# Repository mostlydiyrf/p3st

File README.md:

# P3ST SSB Transceiver
This repository is for design files, Arduino firmware, and assembly instructions.

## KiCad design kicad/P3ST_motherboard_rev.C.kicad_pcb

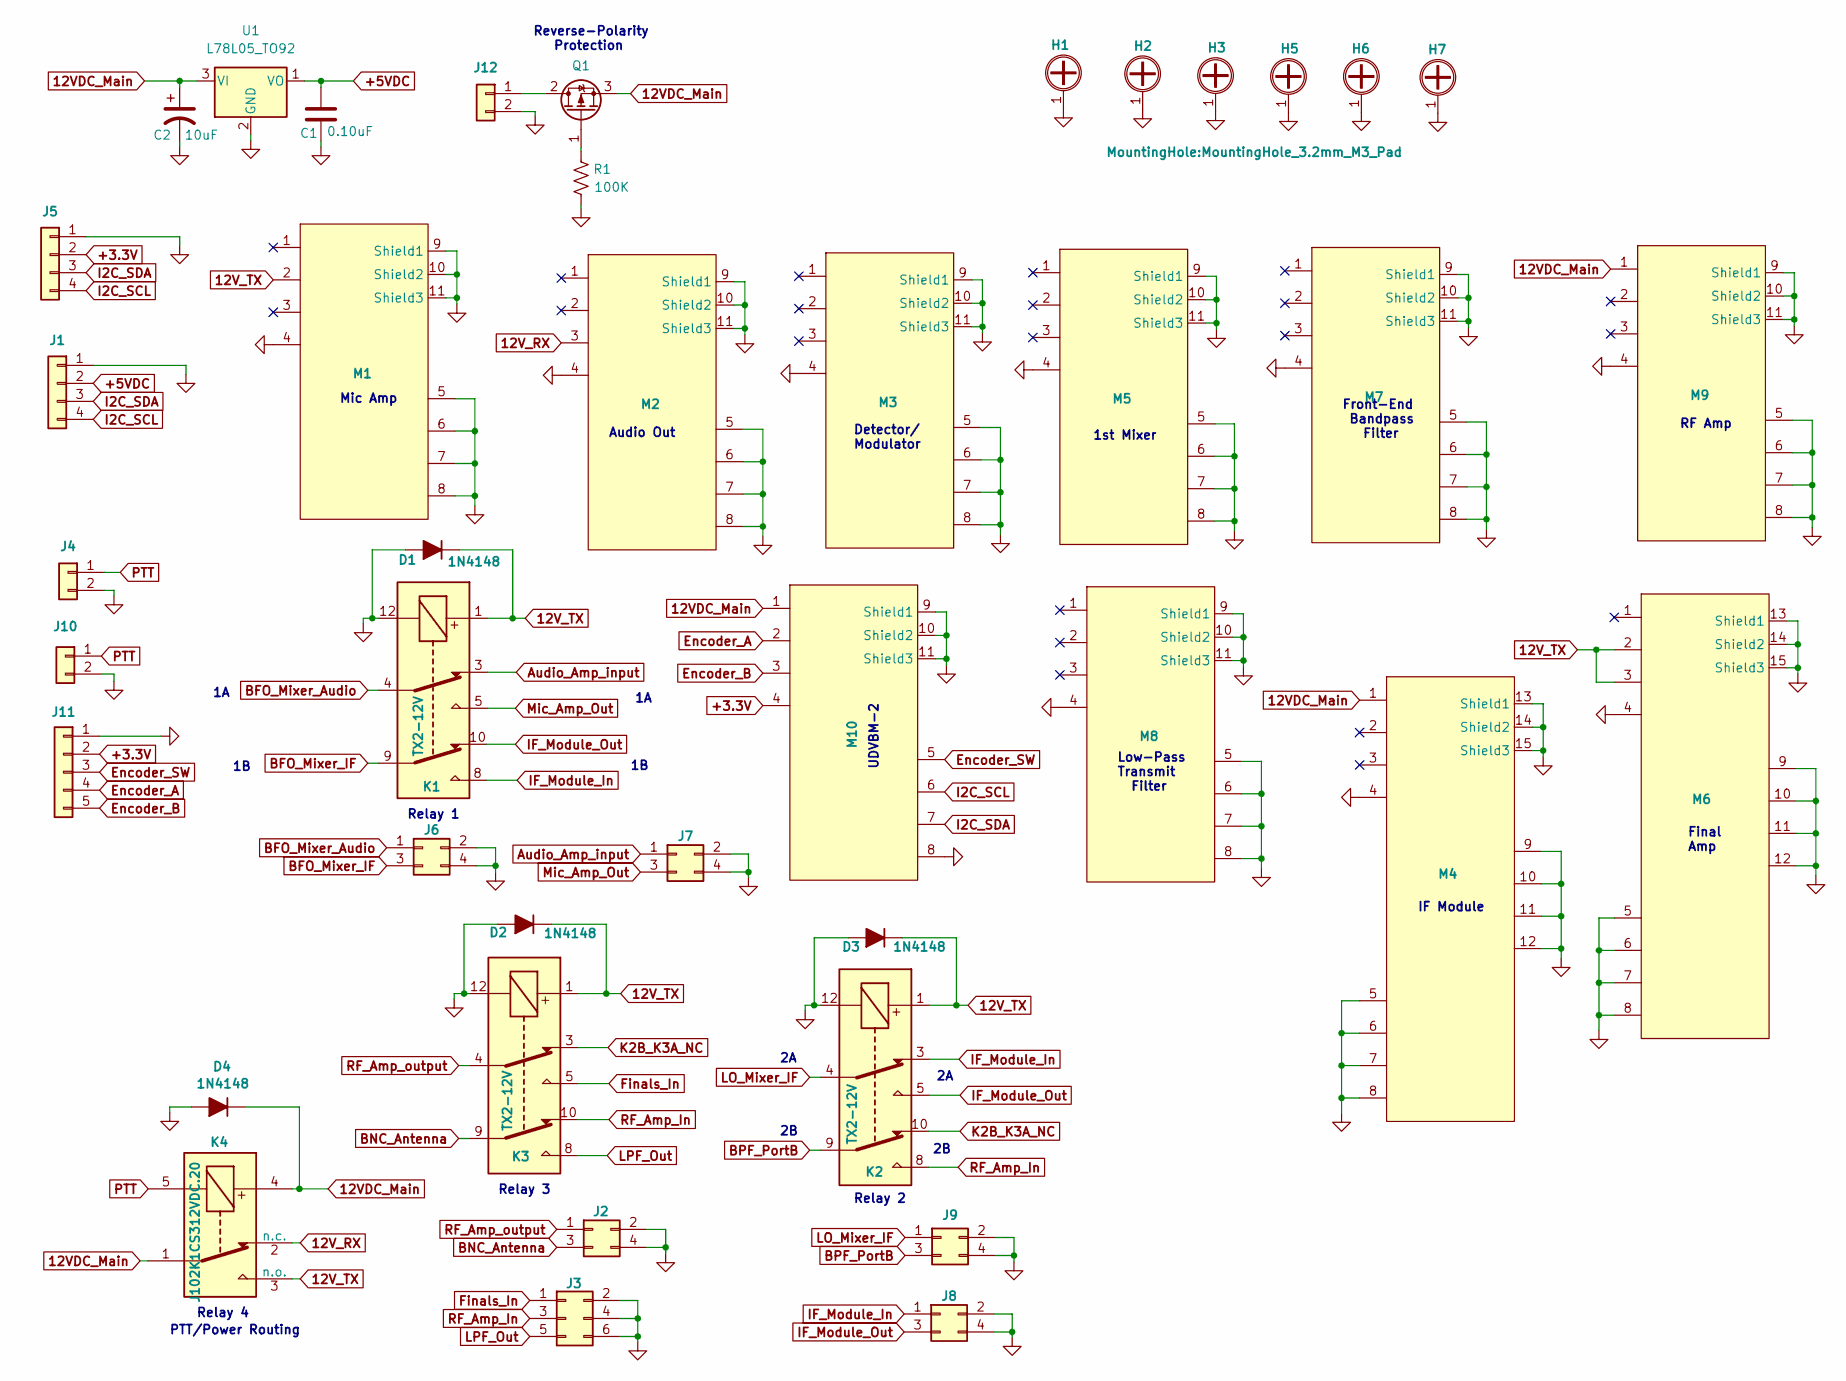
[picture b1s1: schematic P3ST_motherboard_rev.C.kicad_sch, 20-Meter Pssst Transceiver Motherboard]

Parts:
C1: 0.10uF; Ceramic_Disk_Capacitor_P5.00mm
C2: 10uF; CP_Radial_D6.3mm_P2.50mm
D1, D2, D3, D4: 1N4148; D_DO-35_SOD27_P7.62mm_Horizontal
H1, H2, H3, H5, H6, H7: Mounting_Hole_4-40; MountingHole_3.2mm_M3_Pad
J1, J5: Conn_01x04; PinHeader_1x04_P2.54mm_Vertical
J2, J6, J7, J8, J9: Conn_02x02_Odd_Even; RG274_2x2_HS
J3: Conn_02x03_Odd_Even; RG274_2x3_HS
J4, J10, J12: Conn_01x02; PinHeader_1x02_P2.54mm_Vertical
J11: Conn_01x05; PinHeader_1x05_P2.54mm_Vertical
K1, K2, K3: TX2-12V; RELAY_TX2_PAN
K4: J102K1CS312VDC.20; J102K-1C
M1, M2, M7, M8, M9, M10: StandardModule_1; K7TFC_CircuitBlock_Module1
M3, M5: StandardModule_1; K7TFC_CircuitBlock_Half_Module1
M4, M6: StandardModule_2; K7TFC_CircuitBlock_Module2
Q1: MOSFET_P_Channel_GDS; TO-220-3_Vertical
R1: 100K; Resistor_Quarter_Watt_P10.16mm_Horizontal
U1: L78L05_TO92; TO-92_Inline

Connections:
12VDC_Main: C2.1, D4.1 (K), K4.1, K4.4, M4.1, M9.1, M10.1, Q1.3 (S), U1.3 (VI)
12V_RX: K4.2 (n.c.), M2.3
12V_TX: D1.1 (K), D2.1 (K), D3.1 (K), K1.1, K2.1, K3.1, K4.3 (n.o.), M1.2, M6.2, M6.3
+3.3V: J5.2, J11.2, M10.4
+5VDC: C1.1, J1.2, U1.1 (VO)
Audio_Amp_input: J7.1, K1.3
BFO_Mixer_Audio: J6.1, K1.4
BFO_Mixer_IF: J6.3, K1.9
BNC_Antenna: J2.3, K3.9
BPF_PortB: J9.3, K2.9
Encoder_A: J11.4, M10.2
Encoder_B: J11.5, M10.3
Encoder_SW: J11.3, M10.5
Finals_In: J3.1, K3.5
GND: C1.2, C2.2, D1.2 (A), D2.2 (A), D3.2 (A), D4.2 (A), H1.1, H2.1, H3.1, H5.1, H6.1, H7.1, J1.1, J2.2, J2.4, J3.2, J3.4, J3.6, J4.2, J5.1, J6.2, J6.4, J7.2, J7.4, J8.2, J8.4, J9.2, J9.4, J10.2, J11.1, J12.2, K1.12, K2.12, K3.12, M1.4, M1.5, M1.6, M1.7, M1.8, M1.9 (Shield1), M1.10 (Shield2), M1.11 (Shield3), M2.4, M2.5, M2.6, M2.7, M2.8, M2.9 (Shield1), M2.10 (Shield2), M2.11 (Shield3), M3.4, M3.5, M3.6, M3.7, M3.8, M3.9 (Shield1), M3.10 (Shield2), M3.11 (Shield3), M4.4, M4.5, M4.6, M4.7, M4.8, M4.9, M4.10, M4.11, M4.12, M4.13 (Shield1), M4.14 (Shield2), M4.15 (Shield3), M5.4, M5.5, M5.6, M5.7, M5.8, M5.9 (Shield1), M5.10 (Shield2), M5.11 (Shield3), M6.4, M6.5, M6.6, M6.7, M6.8, M6.9, M6.10, M6.11, M6.12, M6.13 (Shield1), M6.14 (Shield2), M6.15 (Shield3), M7.4, M7.5, M7.6, M7.7, M7.8, M7.9 (Shield1), M7.10 (Shield2), M7.11 (Shield3), M8.4, M8.5, M8.6, M8.7, M8.8, M8.9 (Shield1), M8.10 (Shield2), M8.11 (Shield3), M9.4, M9.5, M9.6, M9.7, M9.8, M9.9 (Shield1), M9.10 (Shield2), M9.11 (Shield3), M10.8, M10.9 (Shield1), M10.10 (Shield2), M10.11 (Shield3), R1.2, U1.2 (GND)
I2C_SCL: J1.4, J5.4, M10.6
I2C_SDA: J1.3, J5.3, M10.7
IF_Module_In: J8.1, K1.8, K2.3
IF_Module_Out: J8.3, K1.10, K2.5
K2B_K3A_NC: K2.10, K3.3
LO_Mixer_IF: J9.1, K2.4
LPF_Out: J3.5, K3.8
Mic_Amp_Out: J7.3, K1.5
unnamed: J12.1, Q1.2 (D)
unnamed: Q1.1 (G), R1.1
PTT: J4.1, J10.1, K4.5
RF_Amp_In: J3.3, K2.8, K3.10
RF_Amp_output: J2.1, K3.4

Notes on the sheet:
Relay 3
1st Mixer
Front-End Bandpass Filter
Audio Out
Relay 1
PTT/Power Routing
Final Amp
Mic Amp
Detector/ Modulator
UDVBM-2
RF Amp
Relay 4
IF Module
Reverse-Polarity Protection
Low-Pass Transmit Filter
Relay 2

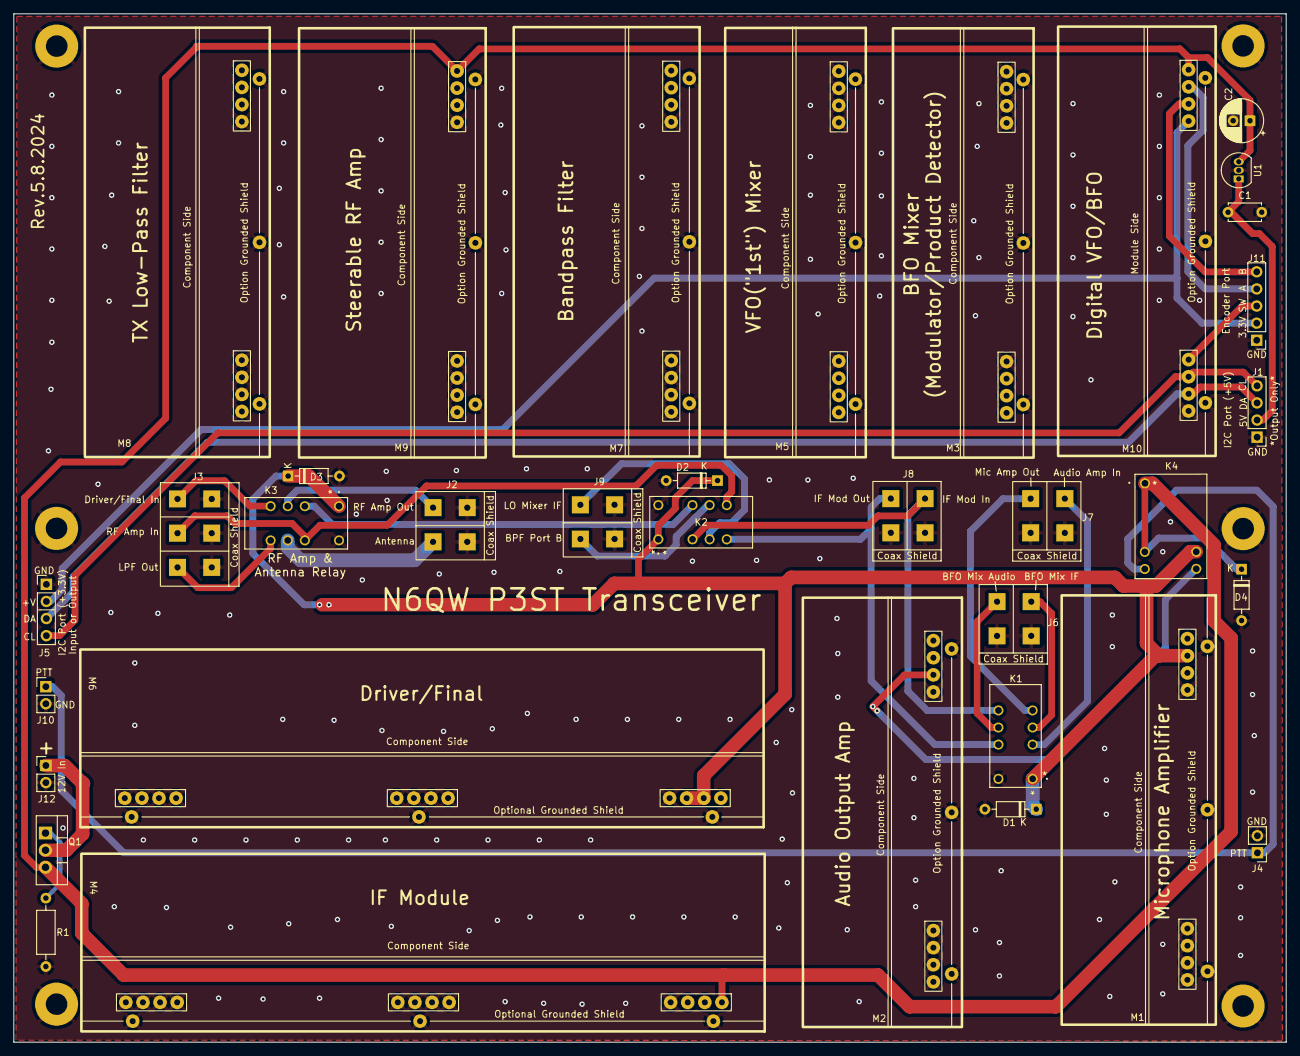
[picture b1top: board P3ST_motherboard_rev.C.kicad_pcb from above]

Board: 2 copper layers, 188.9 x 152.7 mm, 41 parts (0 on the bottom side), 28 nets.

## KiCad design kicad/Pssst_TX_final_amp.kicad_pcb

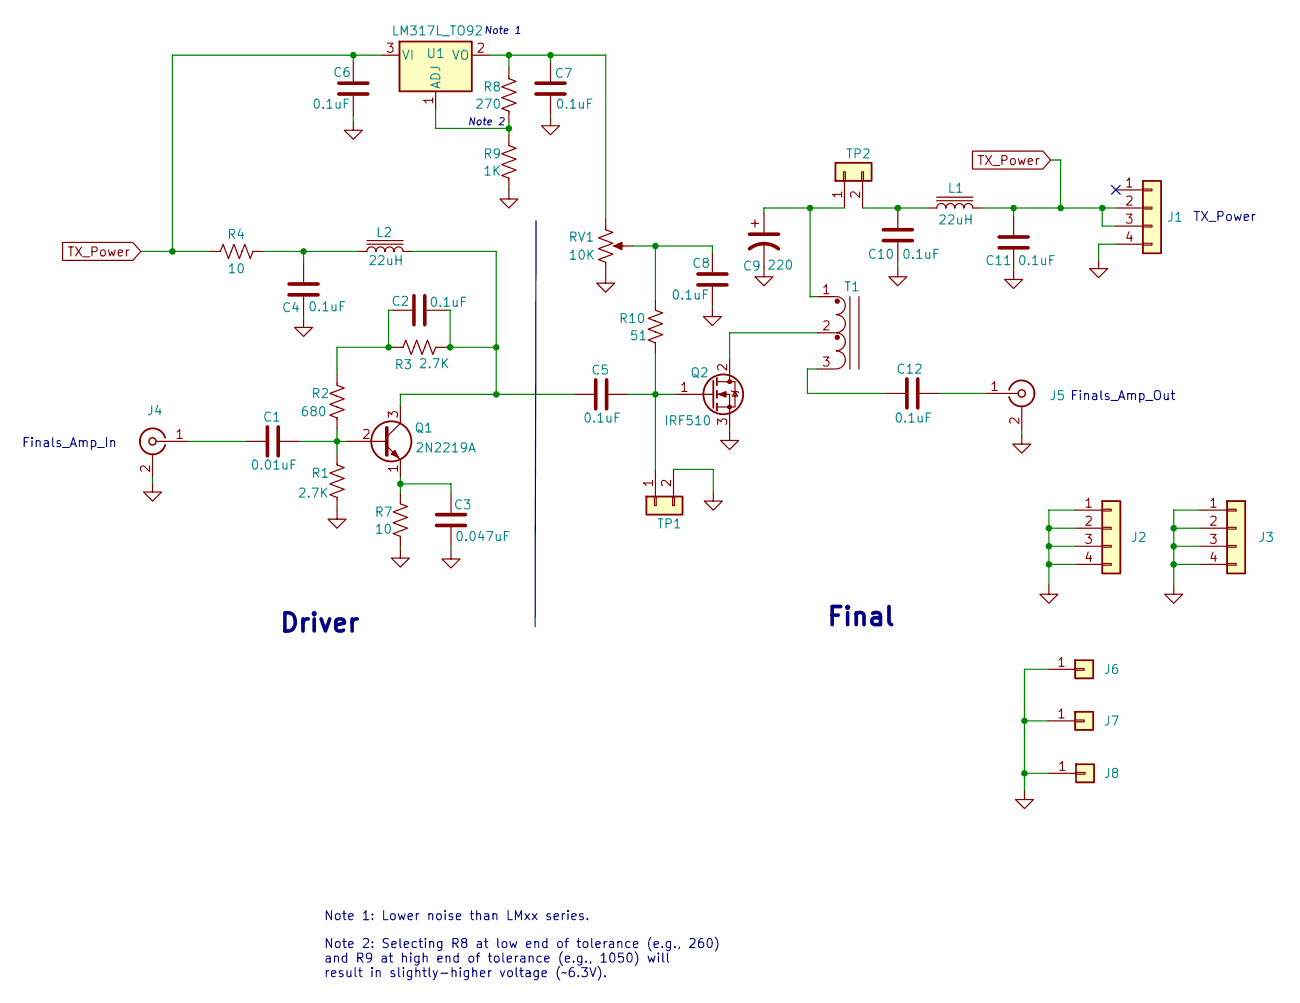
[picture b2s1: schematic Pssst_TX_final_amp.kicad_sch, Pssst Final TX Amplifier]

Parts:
C1: 0.01uF; Ceramic_Disk_Capacitor_P5.00mm
C2, C4, C5, C6, C7, C8, C10, C11, C12: 0.1uF; Ceramic_Disk_Capacitor_P5.00mm
C3: 0.047uF; Ceramic_Disk_Capacitor_P5.00mm
C9: 220; CP_Radial_D5.0mm_P2.50mm
J1, J2, J3: Conn_01x04; PinHeader_1x04_P2.54mm_Vertical
J4, J5: Phono_Jack_RCA; SMA_EdgeMount_0.062_Samtec_wHoles
J6, J7, J8: Conn_01x01; PinHeader_1x01_P2.54mm_Vertical
L1: 22uH; L_Radial_D8.7mm_P5.00mm_Fastron_07HCP
L2: 22uH; L_Axial_L11.0mm_D4.5mm_P15.24mm_Horizontal_Fastron_MECC
Q1: 2N2219A; TO-39-3
Q2: IRF510; TO-220-3_Vertical
R1, R3: 2.7K; Resistor_Quarter_Watt_P10.16mm_Horizontal
R2: 680; Resistor_Quarter_Watt_P10.16mm_Horizontal
R4, R7: 10; Resistor_Quarter_Watt_P10.16mm_Horizontal
R8: 270; Resistor_Quarter_Watt_P10.16mm_Horizontal
R9: 1K; Resistor_Quarter_Watt_P10.16mm_Horizontal
R10: 51; Resistor_Quarter_Watt_P10.16mm_Horizontal
RV1: 10K; POT_Bourns_3362P
T1: Transformer_Bifilar_CT_Toroid; Toroid_Transformer_Bifilar_T50_Vertical_P2.54mm
TP1, TP2: Conn_01x02; PinHeader_1x02_P2.54mm_Vertical
U1: LM317L_TO92; TO-92_Inline

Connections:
GND: C3.1, C4.2, C6.2, C7.2, C8.2, C9.2, C10.2, C11.2, J1.4, J2.1, J2.2, J2.3, J2.4, J3.1, J3.2, J3.3, J3.4, J4.2 (Ext), J5.2 (Ext), J6.1, J7.1, J8.1, Q2.3 (S), R1.2, R7.2, R9.2, RV1.3, TP1.2
unnamed: C1.1, Q1.2 (B), R1.1, R2.2
unnamed: C1.2, J4.1 (In)
unnamed: C2.1, R2.1, R3.1
unnamed: C2.2, C5.2, L2.2, Q1.3 (C), R3.2
unnamed: C3.2, Q1.1 (E), R7.1
unnamed: C4.1, L2.1, R4.2
unnamed: C5.1, Q2.1 (G), R10.2, TP1.1
unnamed: C7.1, R8.1, RV1.1, U1.2 (VO)
unnamed: C8.1, R10.1, RV1.2
unnamed: C9.1, T1.1 (PR1), TP2.1
unnamed: C10.1, L1.1, TP2.2
unnamed: C12.1, T1.3 (PR2)
unnamed: C12.2, J5.1 (In)
unnamed: Q2.2 (D), T1.2 (PM)
unnamed: R8.2, R9.1, U1.1 (ADJ)
TX_Power: C6.1, C11.1, J1.2, J1.3, L1.2, R4.1, U1.3 (VI)

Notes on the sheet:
Driver
Note 2
Note 2: Selecting R8 at low end of tolerance (e.g., 260) and R9 at high end of tolerance (e.g., 1050) will result in slightly-higher voltage (~6.3V).
Finals_Amp_Out
Finals_Amp_In
Final
Note 1: Lower noise than LMxx series.
Note 1
TX_Power

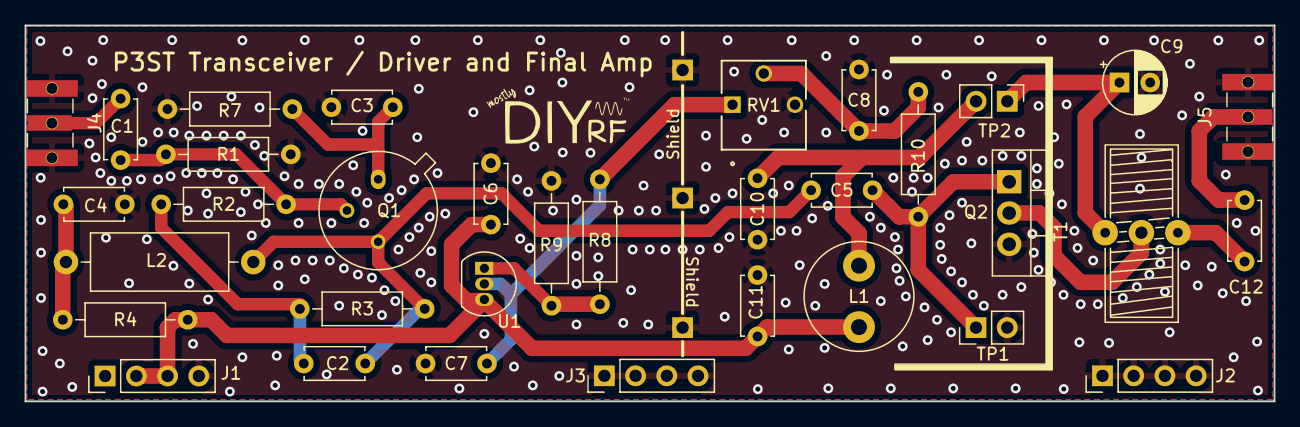
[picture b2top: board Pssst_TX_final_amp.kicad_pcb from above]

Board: 2 copper layers, 101.6 x 30.6 mm, 37 parts (0 on the bottom side), 17 nets.

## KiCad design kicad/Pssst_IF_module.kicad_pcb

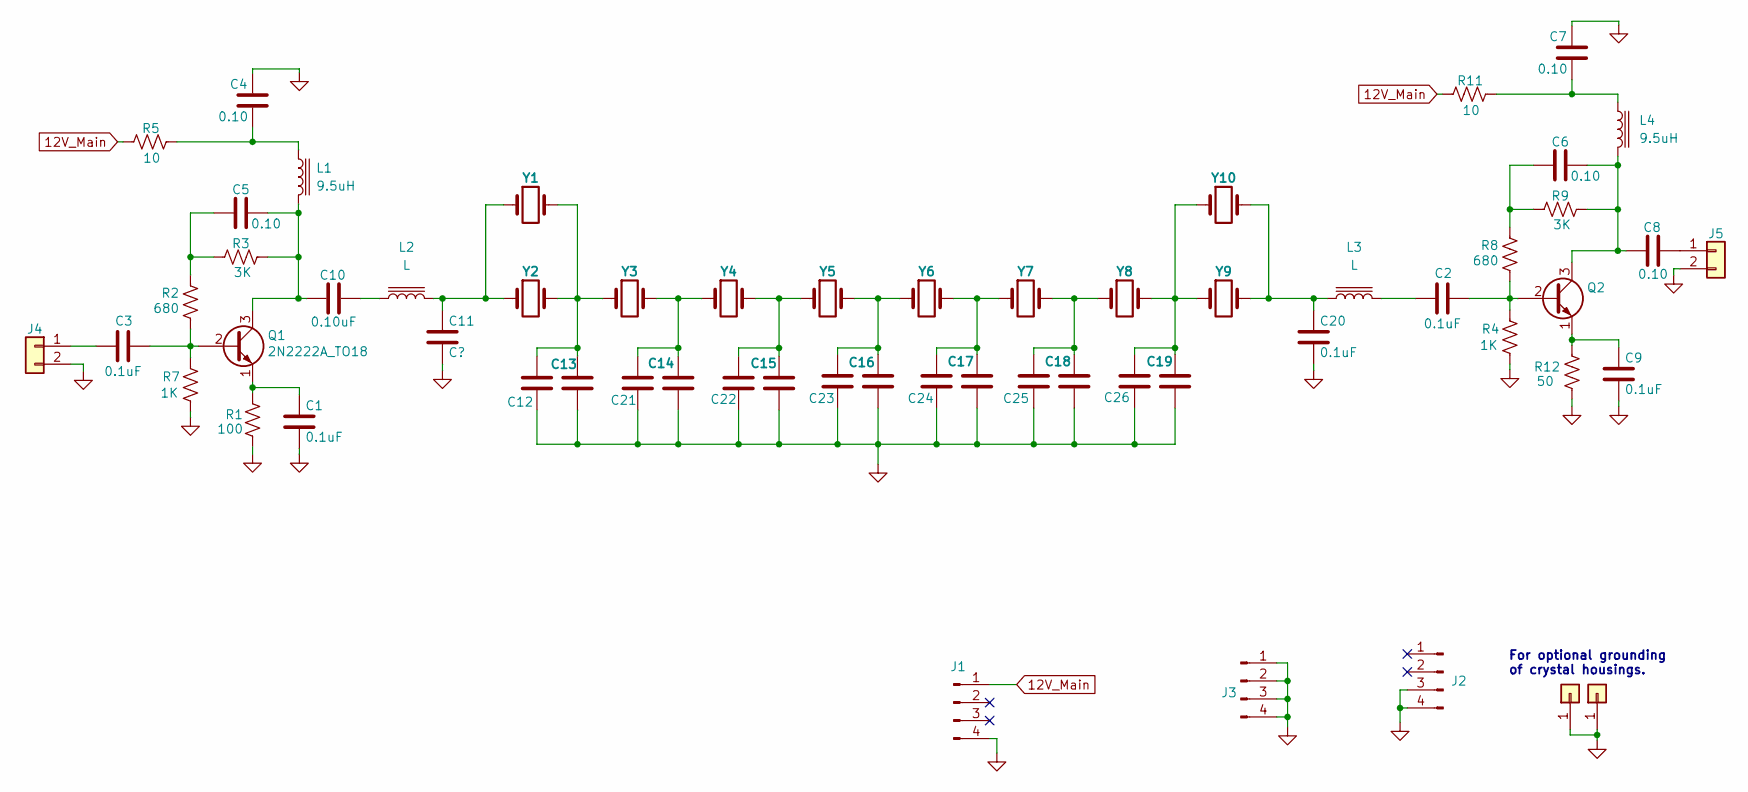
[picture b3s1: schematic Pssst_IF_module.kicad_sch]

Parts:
C1, C2, C3, C9, C20: 0.1uF; C_Disc_D3.4mm_W2.1mm_P2.50mm
C4, C5, C6, C7, C8: 0.10; C_Disc_D3.4mm_W2.1mm_P2.50mm
C10: 0.10uF; C_Disc_D3.4mm_W2.1mm_P2.50mm
C11: C?; C_Disc_D3.4mm_W2.1mm_P2.50mm
C12, C21, C22, C23, C24, C25, C26: C; Cap_ParallelPads_Righthand_P2.50mm
C13, C14, C15, C16, C17, C18, C19: C; C_Disc_D3.4mm_W2.1mm_P2.50mm
J1, J2, J3: Conn_01x04_Male; PinHeader_1x04_P2.54mm_Vertical
J4, J5: Conn_01x02; SMA_EdgeMount_0.062_Samtec_wHoles
J6, J7: Conn_01x01; PinHeader_1x01_P2.54mm_Vertical
L1, L4: 9.5uH; L_Axial_L11.0mm_D4.5mm_P7.62mm_Vertical_Fastron_MECC
L2, L3: L; Toroid_T50_Vertical_P6.00mm
Q1, Q2: 2N2222A_TO18; TO-18-3
R1: 100; R_Axial_P2.54mm_Vertical
R2, R8: 680; R_Axial_P2.54mm_Vertical
R3, R9: 3K; R_Axial_P2.54mm_Vertical
R4, R7: 1K; R_Axial_P2.54mm_Vertical
R5, R11: 10; R_Axial_P2.54mm_Vertical
R12: 50; R_Axial_P2.54mm_Vertical
Y1, Y2, Y3, Y4, Y5, Y6, Y7, Y8, Y9, Y10: Crystal; Crystal_HC49-U_Vertical

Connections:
12V_Main: J1.1, R5.1, R11.1
GND: C1.2, C4.2, C7.2, C9.2, C11.2, C12.2, C13.2, C14.2, C15.2, C16.2, C17.2, C18.2, C19.2, C20.2, C21.2, C22.2, C23.2, C24.2, C25.2, C26.2, J1.4, J2.3, J2.4, J3.1, J3.2, J3.3, J3.4, J4.2, J5.2, J6.1, J7.1, R1.2, R4.2, R7.2, R12.2
unnamed: C1.1, Q1.1 (E), R1.1
unnamed: C2.1, L3.2
unnamed: C2.2, Q2.2 (B), R4.1, R8.2
unnamed: C3.1, J4.1
unnamed: C3.2, Q1.2 (B), R2.2, R7.1
unnamed: C4.1, L1.1, R5.2
unnamed: C5.2, R2.1, R3.1
unnamed: C6.1, C8.1, L4.2, Q2.3 (C), R9.2
unnamed: C6.2, R8.1, R9.1
unnamed: C7.1, L4.1, R11.2
unnamed: C8.2, J5.1
unnamed: C9.1, Q2.1 (E), R12.1
unnamed: C5.1, C10.1, L1.2, Q1.3 (C), R3.2
unnamed: C10.2, L2.1
unnamed: C11.1, L2.2, Y1.1, Y2.1
unnamed: C12.1, C13.1, Y1.2, Y2.2, Y3.1
unnamed: C14.1, C21.1, Y3.2, Y4.1
unnamed: C15.1, C22.1, Y4.2, Y5.1
unnamed: C16.1, C23.1, Y5.2, Y6.1
unnamed: C17.1, C24.1, Y6.2, Y7.1
unnamed: C18.1, C25.1, Y7.2, Y8.1
unnamed: C19.1, C26.1, Y8.2, Y9.1, Y10.1
unnamed: C20.1, L3.1, Y9.2, Y10.2

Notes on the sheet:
For optional grounding of crystal housings.

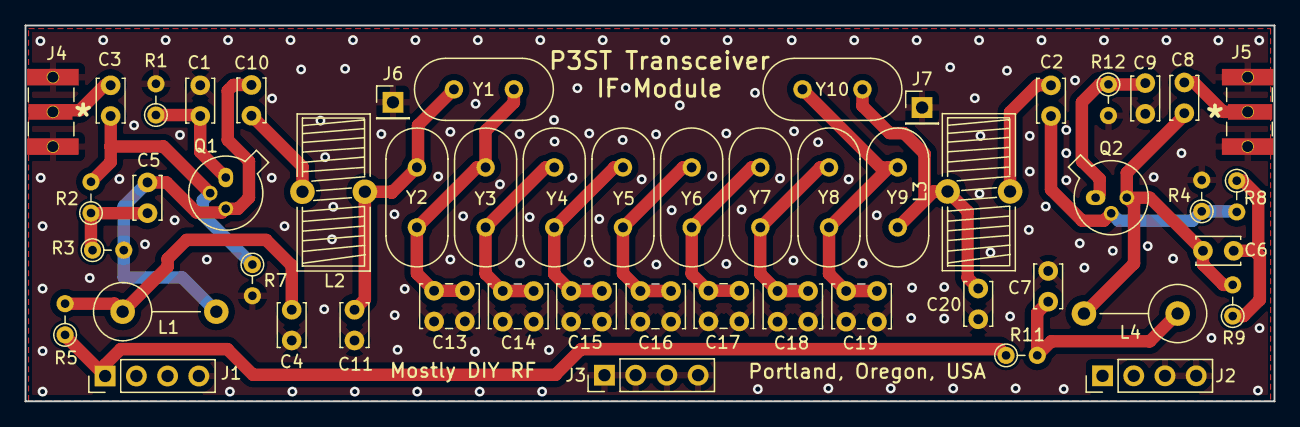
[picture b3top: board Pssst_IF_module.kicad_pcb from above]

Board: 2 copper layers, 101.6 x 30.6 mm, 59 parts (0 on the bottom side), 25 nets.

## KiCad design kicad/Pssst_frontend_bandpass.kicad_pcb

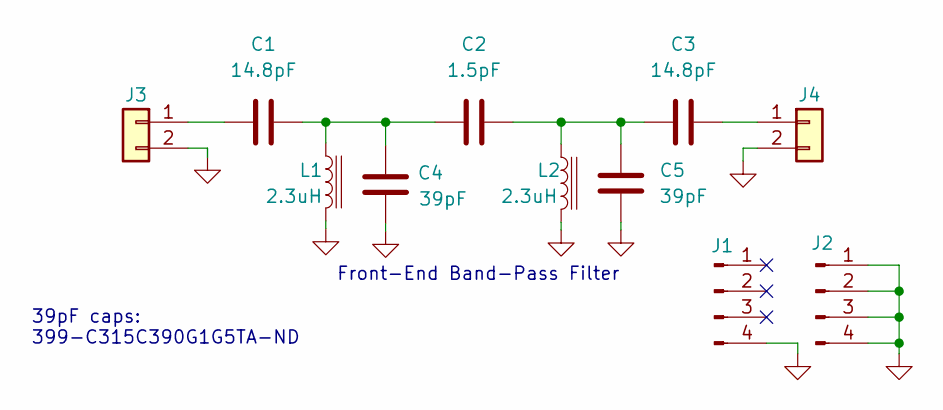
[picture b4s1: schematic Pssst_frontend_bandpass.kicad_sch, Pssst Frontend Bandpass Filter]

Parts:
C1, C3: 14.8pF; Capacitor_Trimmer_Ceramic_GKGxx015_Series
C2: 1.5pF; C_Gimmick
C4, C5: 39pF; Capacitor_Trimmer_Ceramic_GKGxx015_Series
J1, J2: Conn_01x04_Male; PinHeader_1x04_P2.54mm_Vertical
J3, J4: Conn_01x02; SMA_EdgeMount_0.062_Samtec_wHoles
L1, L2: 2.3uH; Toroid_T50_Vertical_P6.00mm

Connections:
GND: C4.2, C5.2, J1.4, J2.1, J2.2, J2.3, J2.4, J3.2, J4.2, L1.2, L2.2
unnamed: C1.1, J3.1
unnamed: C1.2, C2.1, C4.1, L1.1
unnamed: C2.2, C3.1, C5.1, L2.1
unnamed: C3.2, J4.1

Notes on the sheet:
Front-End Band-Pass Filter
39pF caps: 399-C315C390G1G5TA-ND

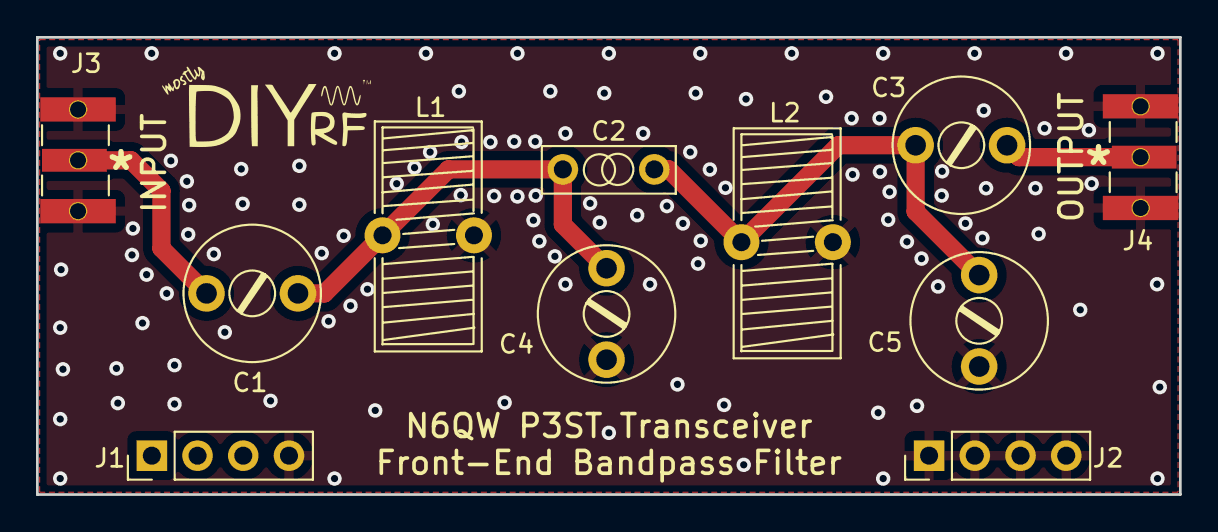
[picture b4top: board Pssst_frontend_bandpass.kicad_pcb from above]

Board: 2 copper layers, 63.5 x 25.4 mm, 11 parts (0 on the bottom side), 5 nets.

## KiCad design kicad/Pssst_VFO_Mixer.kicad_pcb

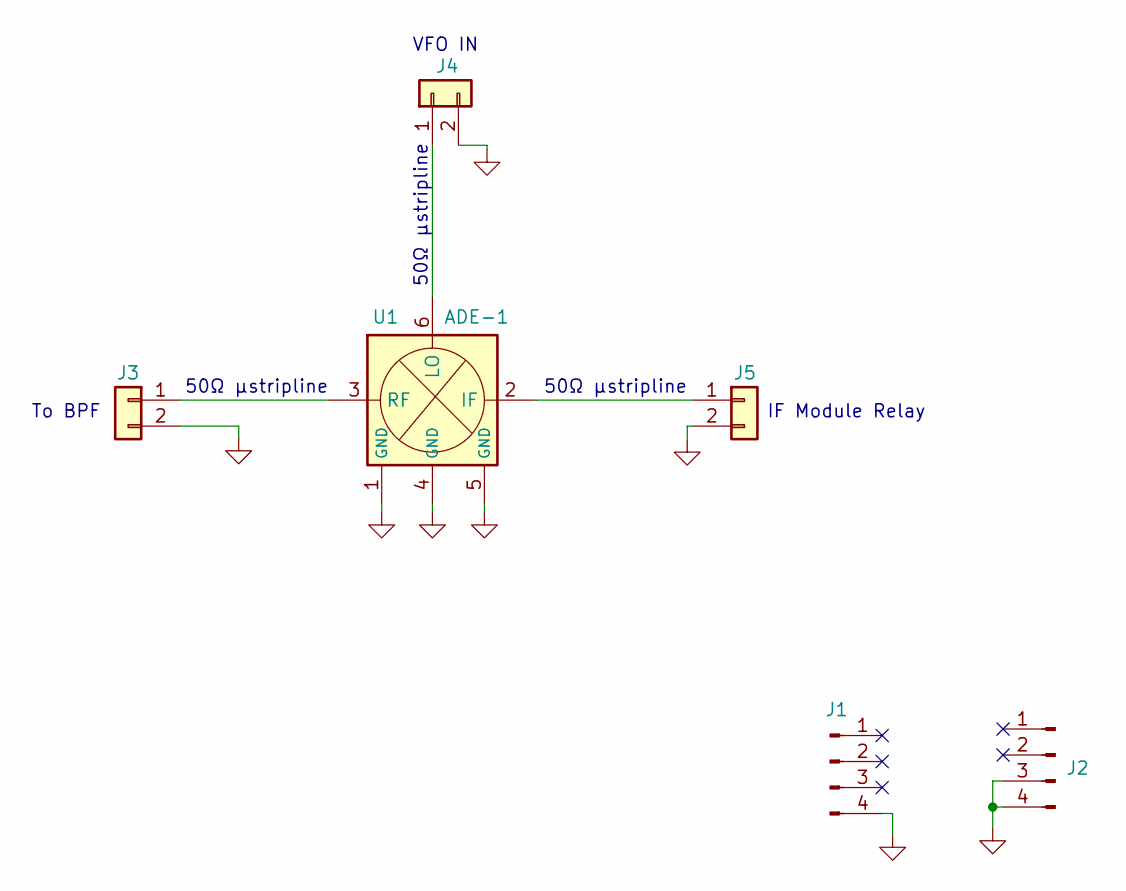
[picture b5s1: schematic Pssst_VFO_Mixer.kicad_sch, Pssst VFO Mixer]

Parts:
J1, J2: Conn_01x04_Male; PinHeader_1x04_P2.54mm_Vertical
J3, J4, J5: Conn_01x02; SMA_EdgeMount_0.062_Samtec_wHoles
U1: ADE-1; Mini-Circuits_ADE-1_CD636

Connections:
GND: J1.4, J2.3, J2.4, J3.2, J4.2, J5.2, U1.1 (GND), U1.4 (GND), U1.5 (GND)
unnamed: J3.1, U1.3 (RF)
unnamed: J4.1, U1.6 (LO)
unnamed: J5.1, U1.2 (IF)

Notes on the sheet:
IF Module Relay
50Ω μstripline
To BPF
VFO IN

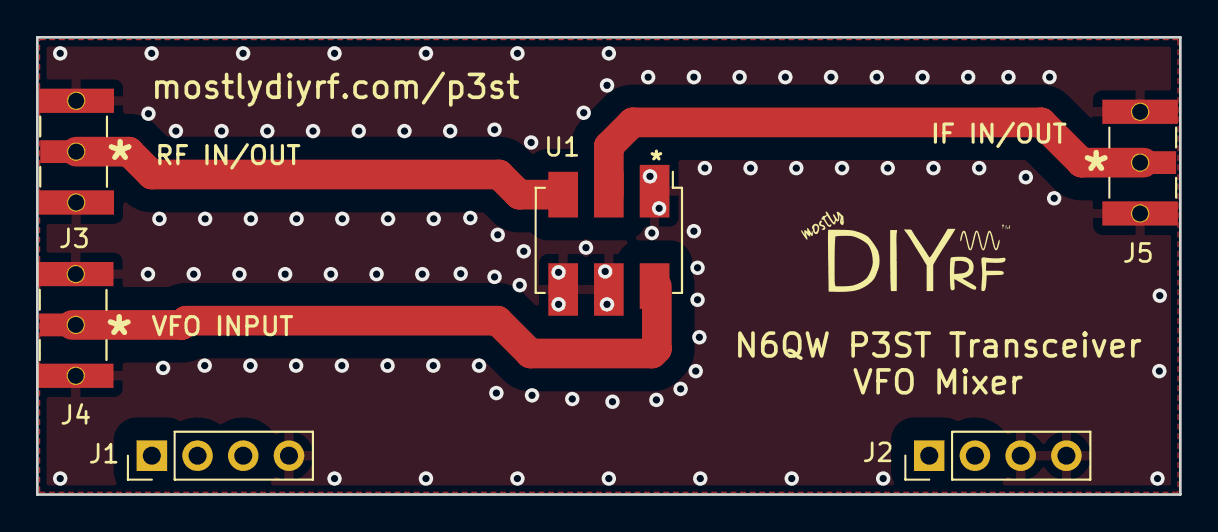
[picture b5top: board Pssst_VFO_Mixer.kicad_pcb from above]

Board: 2 copper layers, 63.5 x 25.4 mm, 6 parts (0 on the bottom side), 4 nets.

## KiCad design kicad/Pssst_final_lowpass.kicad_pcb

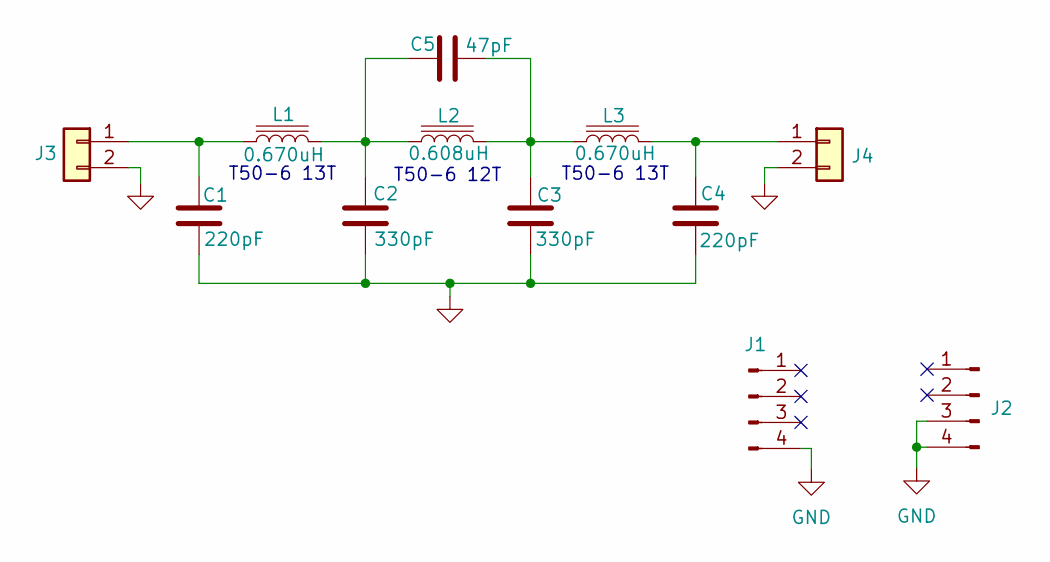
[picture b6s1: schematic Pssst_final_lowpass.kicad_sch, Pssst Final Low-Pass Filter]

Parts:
C1, C4: 220pF; Ceramic_Disk_Capacitor_P5.00mm
C2, C3: 330pF; Ceramic_Disk_Capacitor_P5.00mm
C5: 47pF; Ceramic_Disk_Capacitor_P5.00mm
J1, J2: Conn_01x04_Male; PinHeader_1x04_P2.54mm_horizontal
J3, J4: Conn_01x02; SMA_EdgeMount_0.062_Samtec_wHoles
L1, L3: 0.670uH; Toroid_T50_Vertical_P6.00mm
L2: 0.608uH; Toroid_T50_Vertical_P6.00mm

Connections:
GND: C1.2, C2.2, C3.2, C4.2, J1.4, J2.3, J2.4, J3.2, J4.2
unnamed: C1.1, J3.1, L1.1
unnamed: C2.1, C5.1, L1.2, L2.1
unnamed: C3.1, C5.2, L2.2, L3.1
unnamed: C4.1, J4.1, L3.2

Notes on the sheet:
T50-6 12T
T50-6 13T

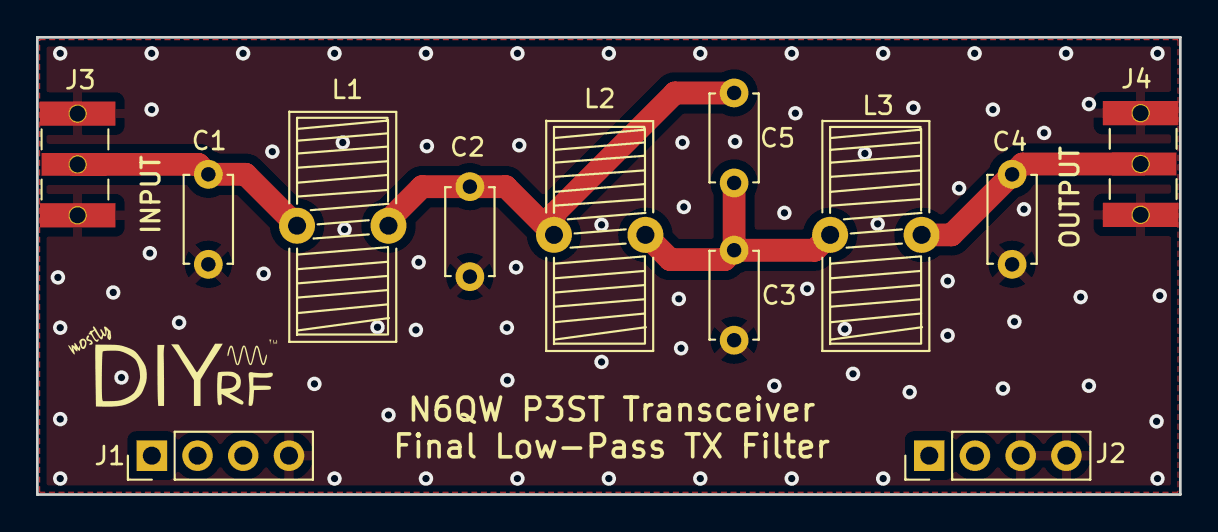
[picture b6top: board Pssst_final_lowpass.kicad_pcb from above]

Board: 2 copper layers, 63.5 x 25.4 mm, 12 parts (0 on the bottom side), 5 nets.

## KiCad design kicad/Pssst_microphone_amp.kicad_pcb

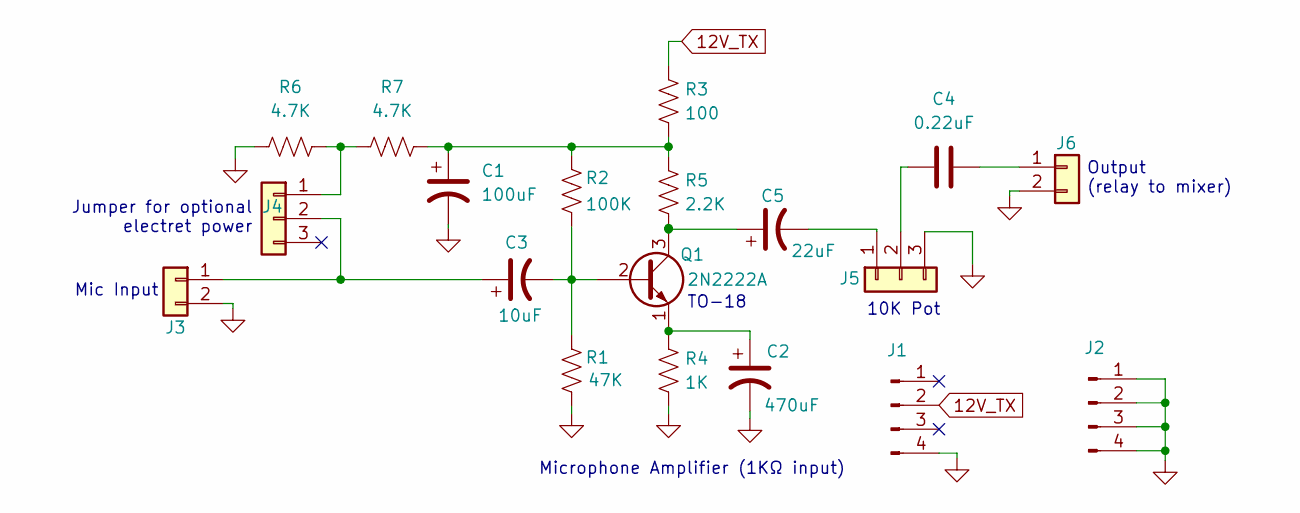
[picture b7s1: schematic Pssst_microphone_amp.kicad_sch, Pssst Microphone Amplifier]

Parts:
C1: 100uF; CP_Radial_D5.0mm_P2.00mm
C2: 470uF; CP_Radial_D8.0mm_P3.50mm
C3: 10uF; CP_Radial_D5.0mm_P2.00mm
C4: 0.22uF; C_Disc_D5.0mm_W2.5mm_P2.50mm
C5: 22uF; CP_Radial_D5.0mm_P2.00mm
J1, J2: Conn_01x04_Male; PinHeader_1x04_P2.54mm_Vertical
J3, J6: Conn_01x02; SMA_EdgeMount_0.062_Samtec_wHoles
J4, J5: Conn_01x03; PinHeader_1x03_P2.54mm_Vertical
Q1: 2N2222A; TO-18-3
R1: 47K; Resistor_Quarter_Watt_P10.16mm_Horizontal
R2: 100K; Resistor_Quarter_Watt_P10.16mm_Horizontal
R3: 100; Resistor_Quarter_Watt_P10.16mm_Horizontal
R4: 1K; Resistor_Quarter_Watt_P10.16mm_Horizontal
R5: 2.2K; Resistor_Quarter_Watt_P10.16mm_Horizontal
R6, R7: 4.7K; Resistor_Quarter_Watt_P10.16mm_Horizontal

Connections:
12V_TX: J1.2, R3.1
GND: C1.2, C2.2, J1.4, J2.1, J2.2, J2.3, J2.4, J3.2, J5.3, J6.2, R1.2, R4.2, R6.1
unnamed: C1.1, R2.1, R3.2, R5.1, R7.2
unnamed: C2.1, Q1.1 (E), R4.1
unnamed: C3.1, J3.1, J4.2
unnamed: C3.2, Q1.2 (B), R1.1, R2.2
unnamed: C4.1, J5.2
unnamed: C4.2, J6.1
unnamed: C5.1, Q1.3 (C), R5.2
unnamed: C5.2, J5.1
unnamed: J4.1, R6.2, R7.1

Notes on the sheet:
Jumper for optional electret power
10K Pot
Output (relay to mixer)
Microphone Amplifier (1KΩ input)
Mic Input
TO-18

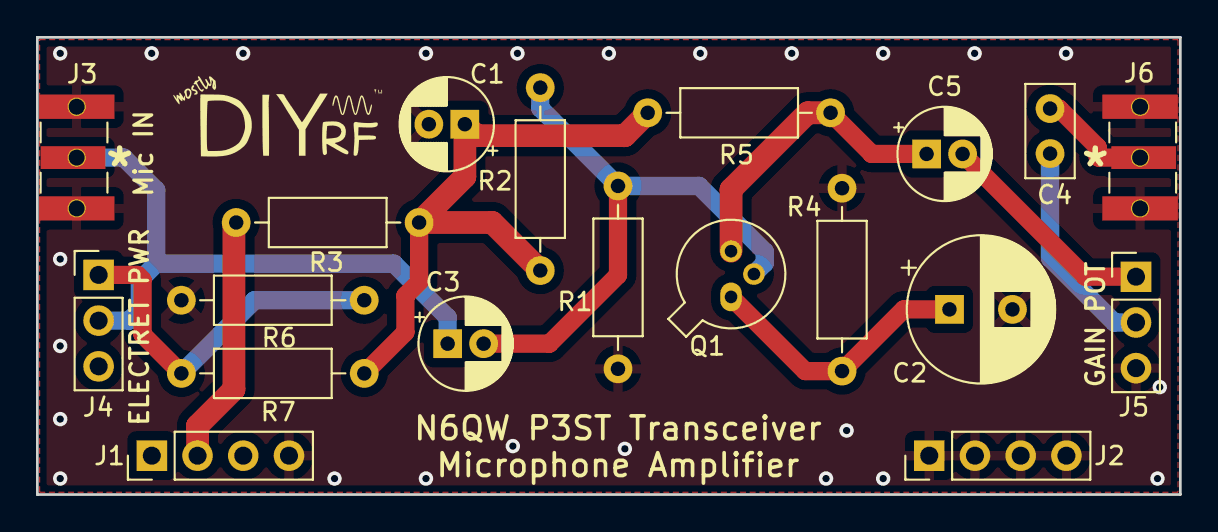
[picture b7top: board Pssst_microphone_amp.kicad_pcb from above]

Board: 2 copper layers, 63.5 x 25.4 mm, 19 parts (0 on the bottom side), 11 nets.

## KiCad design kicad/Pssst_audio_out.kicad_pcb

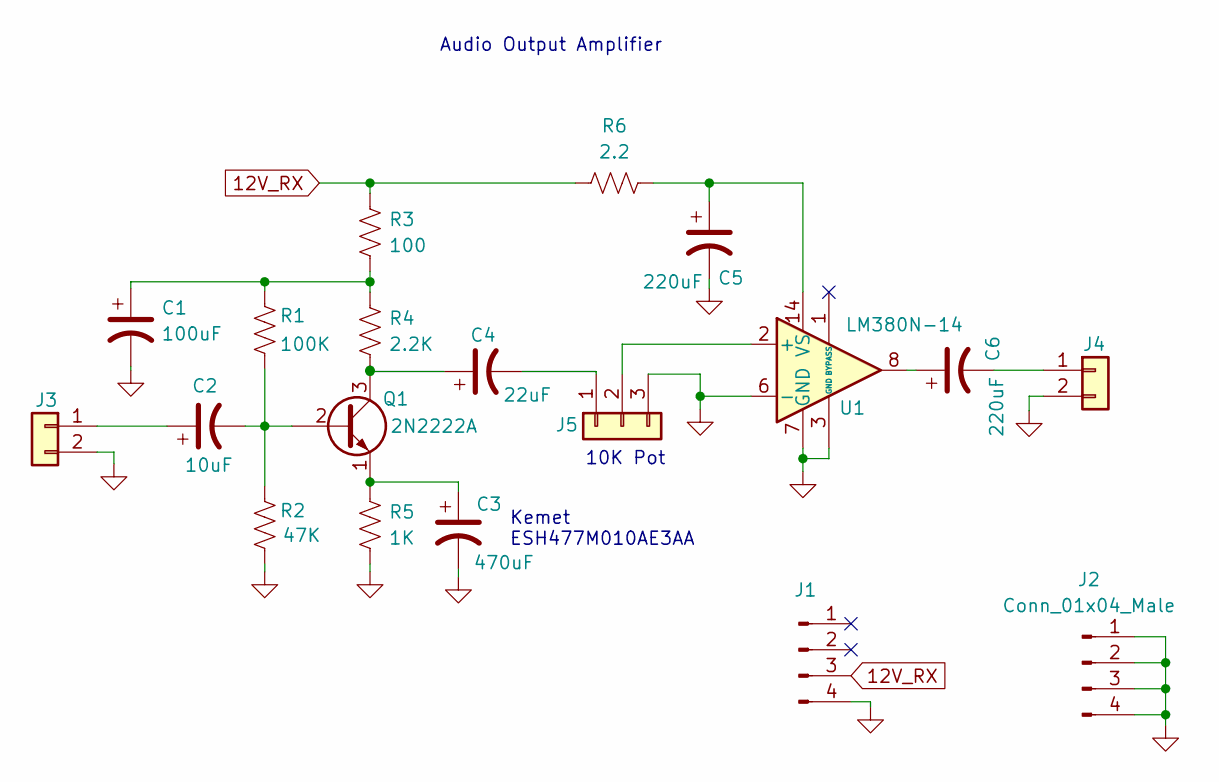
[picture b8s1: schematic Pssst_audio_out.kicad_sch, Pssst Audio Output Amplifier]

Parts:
C1: 100uF; CP_Radial_D5.0mm_P2.00mm
C2: 10uF; CP_Radial_D5.0mm_P2.00mm
C3: 470uF; CP_Radial_D6.3mm_P2.50mm
C4: 22uF; CP_Radial_D5.0mm_P2.00mm
C5, C6: 220uF; CP_Radial_D5.0mm_P2.00mm
J1, J2: Conn_01x04_Male; PinHeader_1x04_P2.54mm_Vertical
J3, J4: Conn_01x02; SMA_EdgeMount_0.062_Samtec_wHoles
J5: Conn_01x03; PinHeader_1x03_P2.54mm_Vertical
Q1: 2N2222A; TO-18-3
R1: 100K; Resistor_Quarter_Watt_P10.16mm_Horizontal
R2: 47K; Resistor_Quarter_Watt_P10.16mm_Horizontal
R3: 100; Resistor_Quarter_Watt_P10.16mm_Horizontal
R4: 2.2K; Resistor_Quarter_Watt_P10.16mm_Horizontal
R5: 1K; Resistor_Quarter_Watt_P10.16mm_Horizontal
R6: 2.2; Resistor_Quarter_Watt_P10.16mm_Horizontal
U1: LM380N-14; DIP-14_W7.62mm

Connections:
12V_RX: J1.3, R3.1, R6.1
GND: C1.2, C3.2, C5.2, J1.4, J2.1, J2.2, J2.3, J2.4, J3.2, J4.2, J5.3, R2.2, R5.2, U1.3 (GND), U1.4 (GND), U1.5 (GND), U1.6 (-), U1.7 (GND), U1.10 (GND), U1.11 (GND), U1.12 (GND)
unnamed: C1.1, R1.1, R3.2, R4.1
unnamed: C2.1, J3.1
unnamed: C2.2, Q1.2 (B), R1.2, R2.1
unnamed: C3.1, Q1.1 (E), R5.1
unnamed: C4.1, Q1.3 (C), R4.2
unnamed: C4.2, J5.1
unnamed: C5.1, R6.2, U1.14 (VS)
unnamed: C6.1, U1.8
unnamed: C6.2, J4.1
unnamed: J5.2, U1.2 (+)

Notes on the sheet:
10K Pot
Kemet ESH477M010AE3AA
Audio Output Amplifier

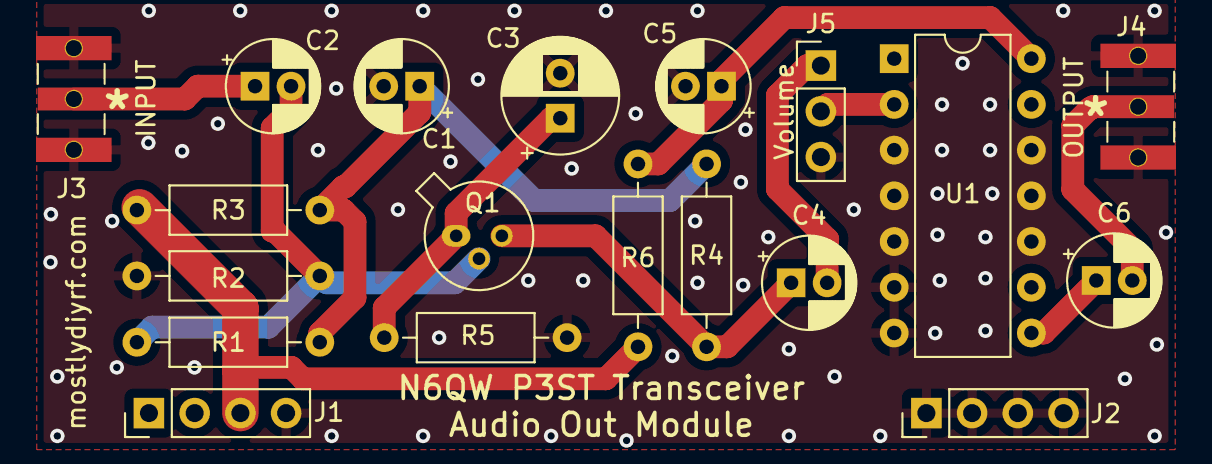
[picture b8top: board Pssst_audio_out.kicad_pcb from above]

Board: 2 copper layers, 19 parts (0 on the bottom side), 12 nets.

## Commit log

2024-02-03 Create .gitignore
    create directory
2024-02-03 Add files via upload
    Pin-number aliases for use with RP2040 boards.
2024-02-04 Add files via upload
    These header files have been modified by K7TFC for 1 second hold time for long_press (was 300ms). There are no accompanying .cpp files.
2024-02-04 Update LICENSE.md
    CC BY-NC-SA 4.0
2024-02-05 Add files via upload
    For the Seeed Studio Xiao RP2040.
2024-02-11 Create references_to_top
2024-02-12 correct file uploaded
2024-03-25 Added comment on K7TFC modification
2024-03-25 Rename firmware/MultiButton.h to firmware/MultiButton/MultiButton.h
2024-03-25 Rename firmware/PinButton.h to firmware/MultiButton/PinButton.h
2024-03-25 Rename firmware/MultiButton/MultiButton.h to firmware/MultiButton/src/MultiButton.h
2024-03-25 Rename firmware/MultiButton/PinButton.h to firmware/MultiButton/src/PinButton.h
2024-03-25 Rename firmware/xiaoRP2040pinNums.h to firmware/src/xiaoRP2040pinNums.h
2024-03-27 Added BFO set, IF offset, & cal. factor functions
2024-03-28 Obsolete version
    Replaced by V2.1
2024-03-28 Latest version
2024-03-29 disabled while(!Serial)
2024-04-03 Added empty BFO EEPROM test
2024-04-03 Added EEPROM conditional tests to setup().
2024-04-10 Added full version number to first line
2024-04-14 To clear EEPROM (make Xiao "look" new to firmware)
2024-04-14 To clear EEPROM (make Xiao "look" new to firmware).
    Upload and run this on the Xiao and then reload the P3ST_xiao.ino sketch. It will then run as if the Xiao had not
    been previously programed and run (i.e., it will not detect any previous values saved in EEPROM).
2024-04-15 Beta version for testing. Please report bugs.
2024-05-04 Rename P3ST_Xiao_V.2.1.2_beta.ino to P3ST_Xiao_V.2.1.2.ino
    name change
2024-07-15 Add files via upload
    Capacitor values and winding data for all HF bands.
2025-01-17 Add files via upload
    Complete and updated list with sources and part numbers

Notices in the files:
kicad/Pssst_IF_module.kicad_pcb:
CC BY-SA 4.0
kicad/Pssst_VFO_Mixer.kicad_pcb:
CC BY-NC 4.0
